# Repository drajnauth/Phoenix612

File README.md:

# Phoenix612
Phoenix612 Transceiver Board

This is the updated `Dueling 612 Tranceiver`.  It contains the KiCad schematic and pcb files as well as other design artifacts.

The project has been renamed to `Phoenix612`

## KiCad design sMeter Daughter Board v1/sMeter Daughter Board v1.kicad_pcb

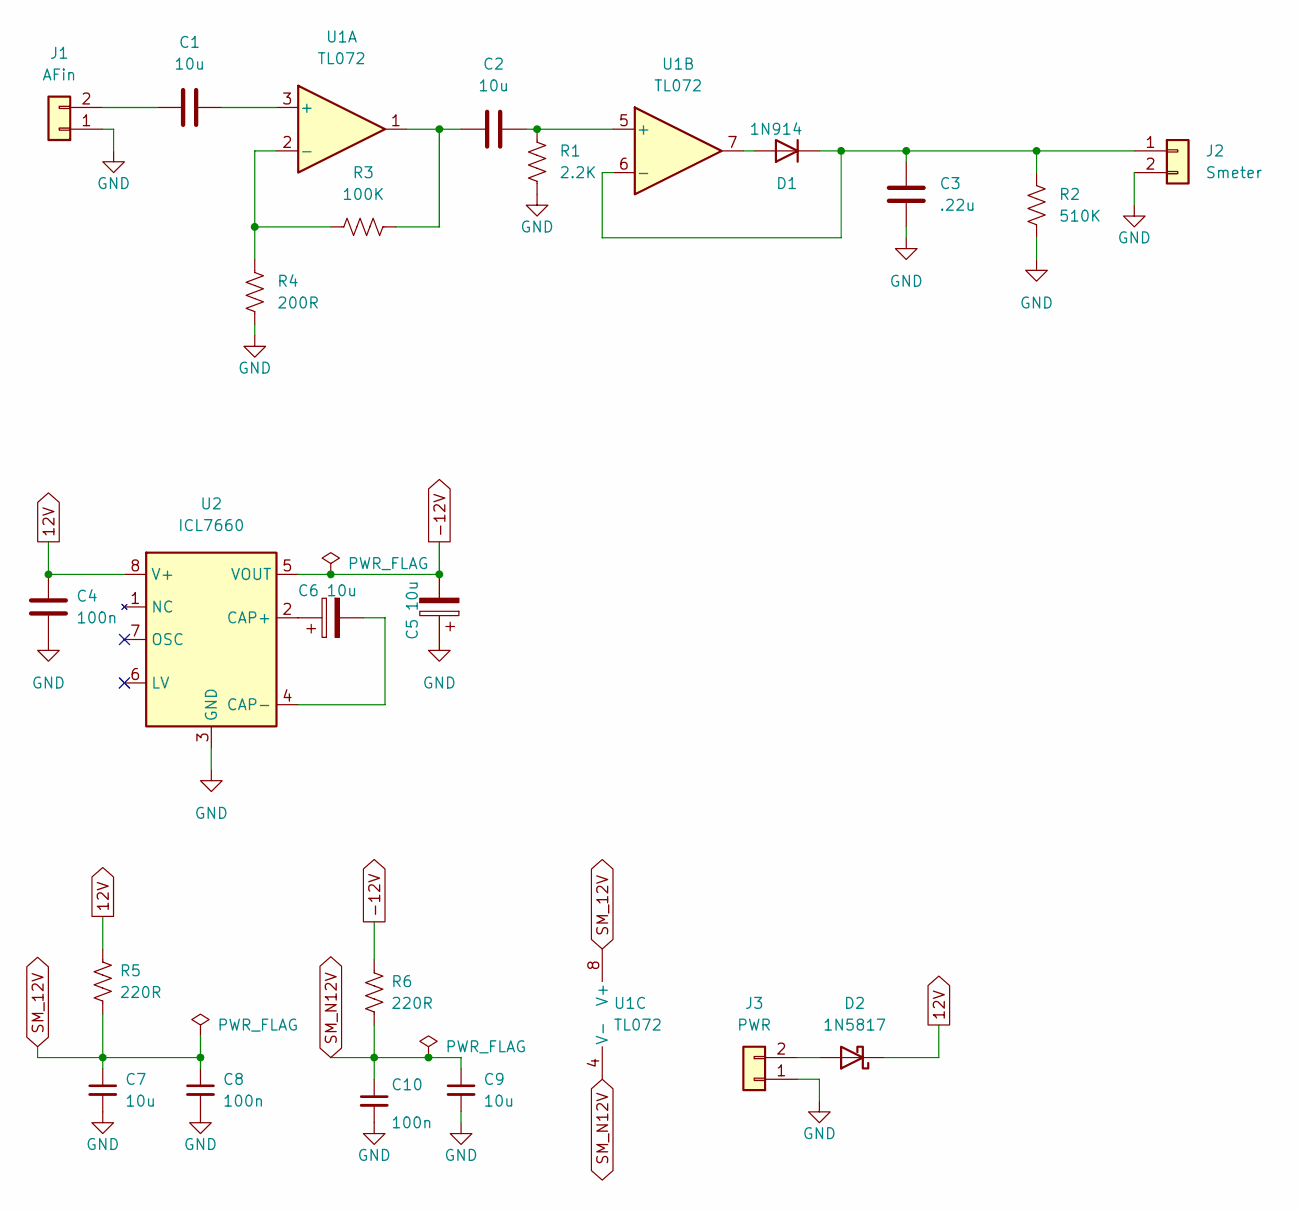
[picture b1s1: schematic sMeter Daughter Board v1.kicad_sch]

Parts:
C1, C2, C7, C9: 10u; C_1206_3216Metric
C3: .22u; C_1206_3216Metric
C4, C8, C10: 100n; C_1206_3216Metric
C5, C6: 10u; CP_Radial_D8.0mm_P2.50mm
D1: 1N914; D_DO-35_SOD27_P7.62mm_Horizontal
D2: 1N5817; D_DO-41_SOD81_P10.16mm_Horizontal
J1: AFin; PinHeader_1x02_P2.54mm_Vertical
J2: Smeter; PinHeader_1x02_P2.54mm_Vertical
J3: PWR; PinHeader_1x02_P2.54mm_Vertical
R1: 2.2K; R_1206_3216Metric
R2: 510K; R_1206_3216Metric
R3: 100K; R_1206_3216Metric
R4: 200R; R_1206_3216Metric
R5, R6: 220R; R_1206_3216Metric
U1: TL072; DIP-8_W7.62mm_Socket
U2: ICL7660; SOIC-8_3.9x4.9mm_P1.27mm

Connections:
12V: C4.2, D2.1 (K), R5.1, U2.8 (V+)
-12V: C5.2, R6.1, U2.5 (VOUT)
GND: C3.2, C4.1, C5.1, C7.2, C8.2, C9.2, C10.2, J1.1, J2.2, J3.1, R1.1, R2.1, R4.2, U2.3 (GND)
unnamed: C1.1, J1.2
unnamed: C1.2, U1.3 (+)
unnamed: C2.1, R3.2, U1.1
unnamed: C2.2, R1.2, U1.5 (+)
unnamed: C3.1, D1.1 (K), J2.1, R2.2, U1.6 (-)
unnamed: C6.1, U2.2 (CAP+)
unnamed: C6.2, U2.4 (CAP-)
unnamed: D1.2 (A), U1.7
unnamed: D2.2 (A), J3.2
unnamed: R3.1, R4.1, U1.2 (-)
SM_12V: C7.1, C8.1, R5.2, U1.8 (V+)
SM_N12V: C9.1, C10.1, R6.2, U1.4 (V-)

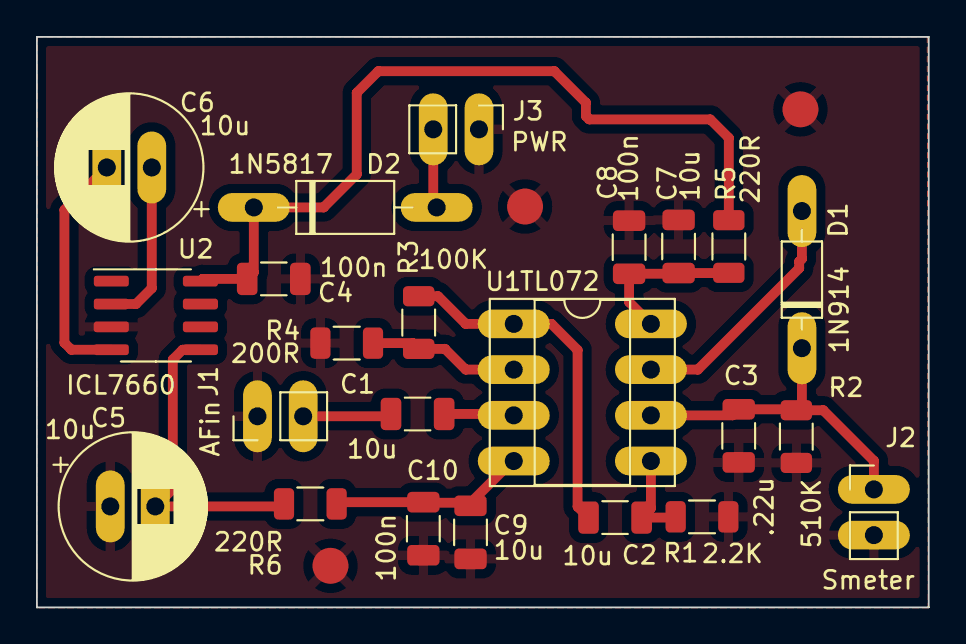
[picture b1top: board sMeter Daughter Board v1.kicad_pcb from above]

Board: 2 copper layers, 49.5 x 31.7 mm, 23 parts (0 on the bottom side), 15 nets.

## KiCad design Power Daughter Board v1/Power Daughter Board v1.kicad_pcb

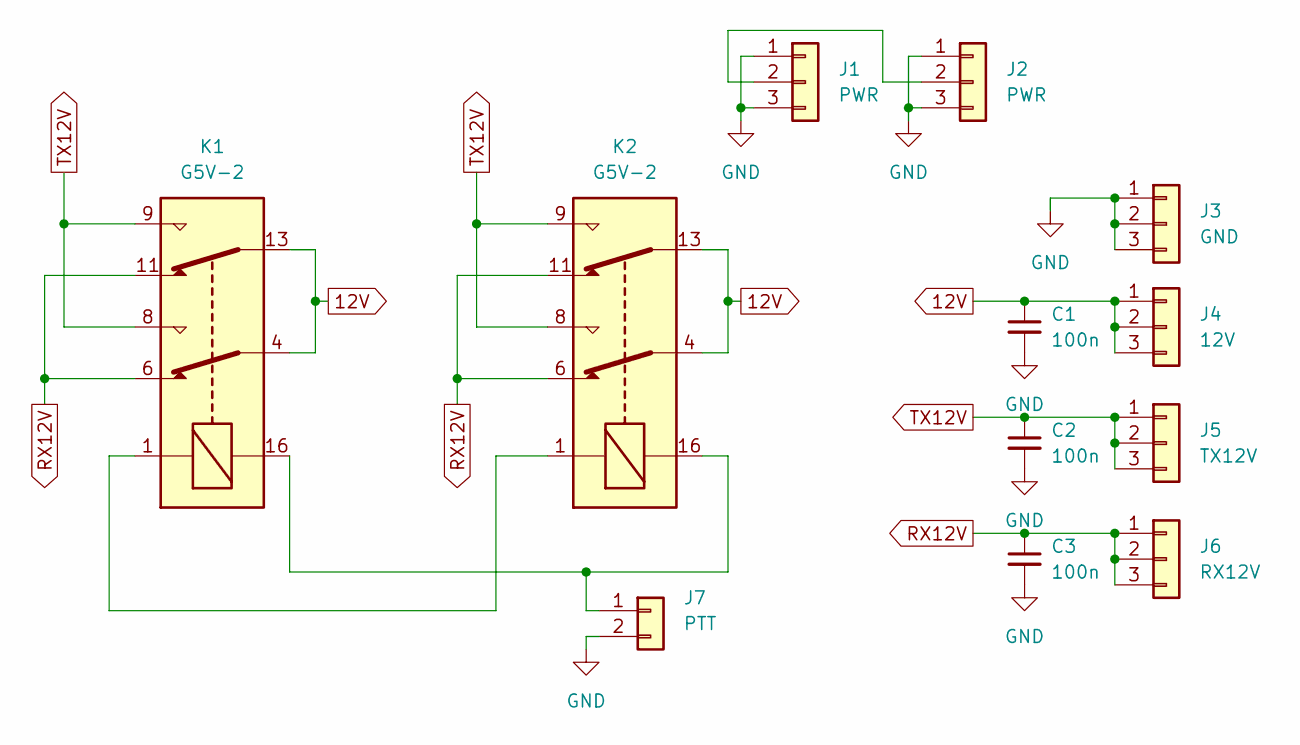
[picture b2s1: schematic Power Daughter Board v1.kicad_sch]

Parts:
C1, C2, C3: 100n; C_1206_3216Metric
J1, J2: PWR; PinHeader_1x03_P2.54mm_Vertical
J3: GND; PinHeader_1x03_P2.54mm_Vertical
J4: 12V; PinHeader_1x03_P2.54mm_Vertical
J5: TX12V; PinHeader_1x03_P2.54mm_Vertical
J6: RX12V; PinHeader_1x03_P2.54mm_Vertical
J7: PTT; PinHeader_1x02_P2.54mm_Vertical
K1, K2: G5V-2; Relay_DPDT_Omron_G5V-2

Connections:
12V: C1.1, J4.1, J4.2, J4.3, K1.4, K1.13, K2.4, K2.13
GND: C1.2, C2.2, C3.2, J1.1, J1.3, J2.1, J2.3, J3.1, J3.2, J3.3, J7.2
unnamed: J1.2, J2.2
unnamed: J7.1, K1.16, K2.16
unnamed: K1.1, K2.1
RX12V: C3.1, J6.1, J6.2, J6.3, K1.6, K1.11, K2.6, K2.11
TX12V: C2.1, J5.1, J5.2, J5.3, K1.8, K1.9, K2.8, K2.9

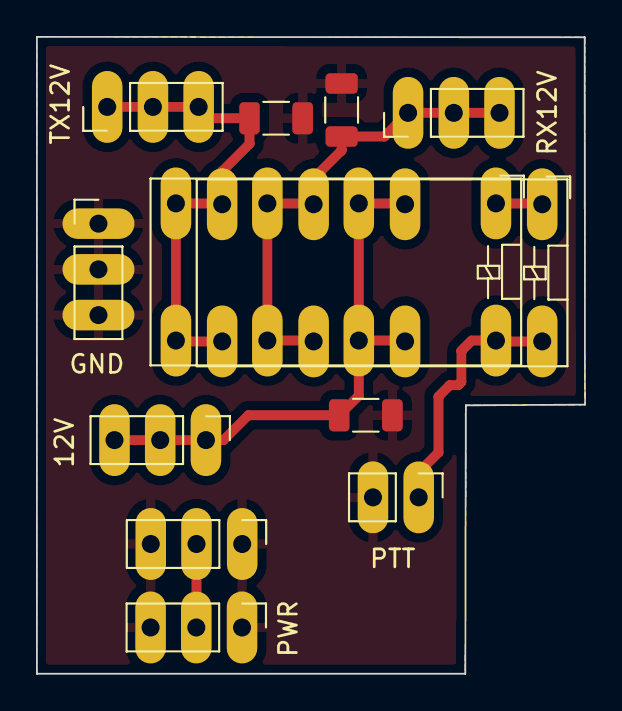
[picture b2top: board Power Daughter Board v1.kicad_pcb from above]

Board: 2 copper layers, 30.5 x 35.4 mm, 12 parts (0 on the bottom side), 7 nets.

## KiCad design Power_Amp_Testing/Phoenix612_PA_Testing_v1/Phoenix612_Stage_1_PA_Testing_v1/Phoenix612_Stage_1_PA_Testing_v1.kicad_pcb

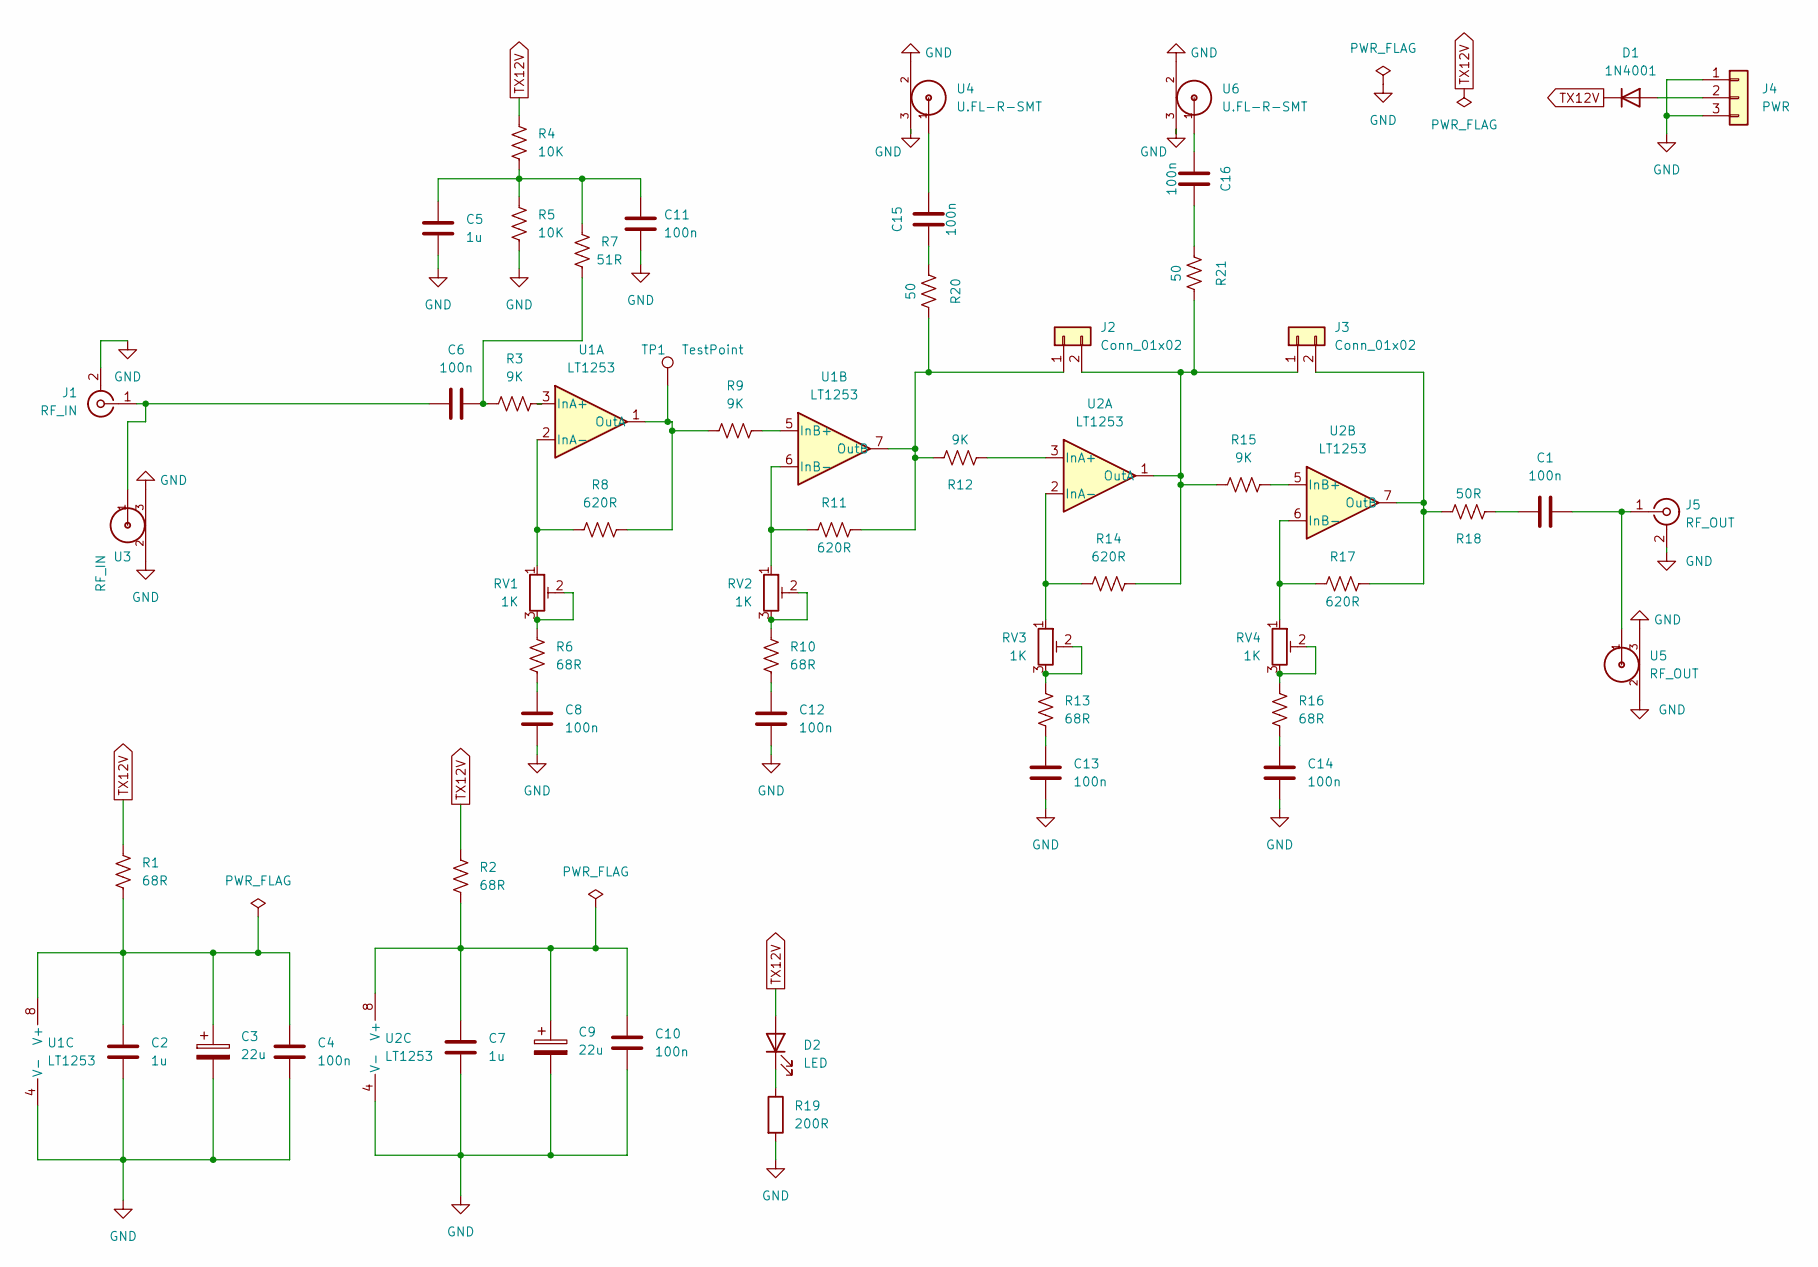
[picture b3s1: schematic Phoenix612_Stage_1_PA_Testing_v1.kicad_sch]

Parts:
C1, C4, C6, C8, C10, C11, C12, C13, C14, C15, C16: 100n; C_1206_3216Metric
C2, C5, C7: 1u; C_1206_3216Metric
C3, C9: 22u; CP_Radial_D8.0mm_P2.50mm
D1: 1N4001; D_DO-41_SOD81_P10.16mm_Horizontal
D2: LED; LED_D3.0mm
J1: RF_IN; SMA_Amphenol_901-144_Vertical
J2, J3: Conn_01x02; PinHeader_1x02_P2.54mm_Vertical
J4: PWR; PinHeader_1x03_P2.54mm_Vertical
J5: RF_OUT; SMA_Amphenol_901-144_Vertical
R1, R2, R6, R10, R13, R16: 68R; R_1206_3216Metric
R3, R9, R12, R15: 9K; R_1206_3216Metric
R4, R5: 10K; R_1206_3216Metric
R7: 51R; R_1206_3216Metric
R8, R11, R14, R17: 620R; R_1206_3216Metric
R18: 50R; R_1206_3216Metric
R19: 200R; R_1206_3216Metric
R20, R21: 50; R_1206_3216Metric
RV1, RV2, RV3, RV4: 1K; Potentiometer_Bourns_3296W_Vertical
TP1: TestPoint; Pin_D0.7mm_L6.5mm_W1.8mm_FlatFork
U1, U2: LT1253; DIP-8_W7.62mm
U3: RF_IN; U.FL-R-SMT
U4, U6: U.FL-R-SMT
U5: RF_OUT; U.FL-R-SMT

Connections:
GND: C2.2, C3.2, C4.2, C5.2, C7.2, C8.2, C9.2, C10.2, C11.2, C12.2, C13.2, C14.2, J1.2 (Ext), J4.1, J4.3, J5.2 (Ext), R5.2, R19.2, U1.4 (V-), U2.4 (V-), U3.2, U3.3, U4.2, U4.3, U5.2, U5.3, U6.2, U6.3
unnamed: C2.1, C3.1, C4.1, R1.2, U1.8 (V+)
unnamed: C6.1, J1.1 (In), U3.1
unnamed: C6.2, R3.1, R7.1
unnamed: C8.1, R6.2
unnamed: C7.1, C9.1, C10.1, R2.2, U2.8 (V+)
unnamed: C5.1, C11.1, R4.2, R5.1, R7.2
unnamed: C12.1, R10.2
unnamed: C13.1, R13.2
unnamed: C14.1, R16.2
unnamed: C15.1, R20.2
unnamed: C15.2, U4.1
unnamed: C16.2, R21.2
unnamed: D1.2 (A), J4.2
unnamed: D2.1 (K), R19.1
unnamed: C1.2, J5.1 (In), U5.1
unnamed: R3.2, U1.3 (InA+)
unnamed: R6.1, RV1.2, RV1.3
unnamed: R8.1, RV1.1, U1.2 (InA-)
unnamed: R8.2, R9.1, TP1.1, U1.1 (OutA)
unnamed: R9.2, U1.5 (InB+)
unnamed: R10.1, RV2.2, RV2.3
unnamed: J2.1, R11.1, R12.1, R20.1, U1.7 (OutB)
unnamed: R11.2, RV2.1, U1.6 (InB-)
unnamed: R13.1, RV3.2, RV3.3
unnamed: R14.1, RV3.1, U2.2 (InA-)
unnamed: J2.2, J3.1, R14.2, R15.1, R21.1, U2.1 (OutA)
unnamed: R15.2, U2.5 (InB+)
unnamed: R16.1, RV4.2, RV4.3
unnamed: J3.2, R17.1, R18.1, U2.7 (OutB)
unnamed: R17.2, RV4.1, U2.6 (InB-)
unnamed: C1.1, R18.2
unnamed: R12.2, U2.3 (InA+)
unnamed: C16.1, U6.1
TX12V: D1.1 (K), D2.2 (A), R1.1, R2.1, R4.1

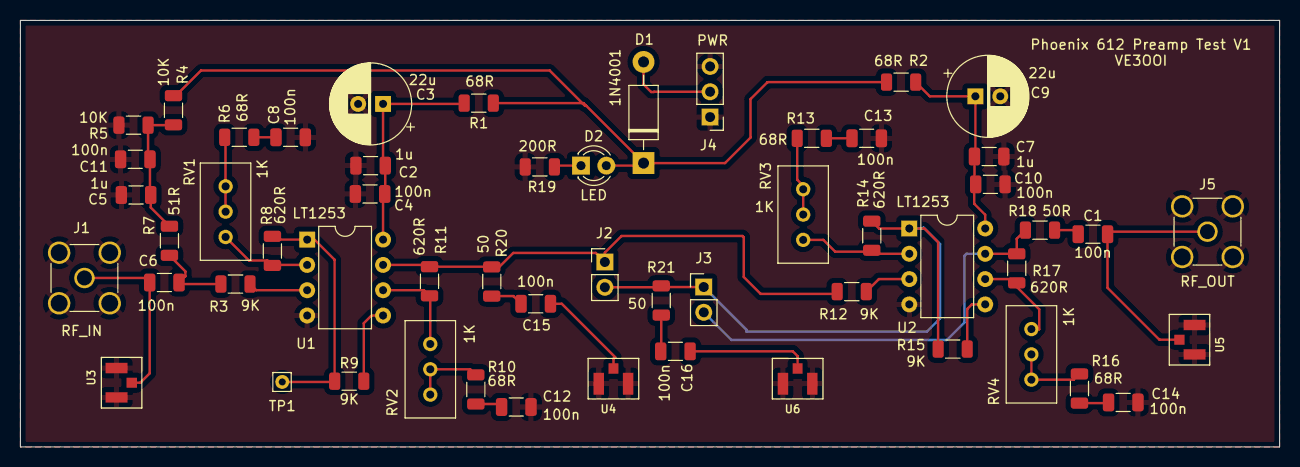
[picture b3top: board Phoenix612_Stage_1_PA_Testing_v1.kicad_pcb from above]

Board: 2 copper layers, 126.4 x 42.8 mm, 55 parts (0 on the bottom side), 35 nets.

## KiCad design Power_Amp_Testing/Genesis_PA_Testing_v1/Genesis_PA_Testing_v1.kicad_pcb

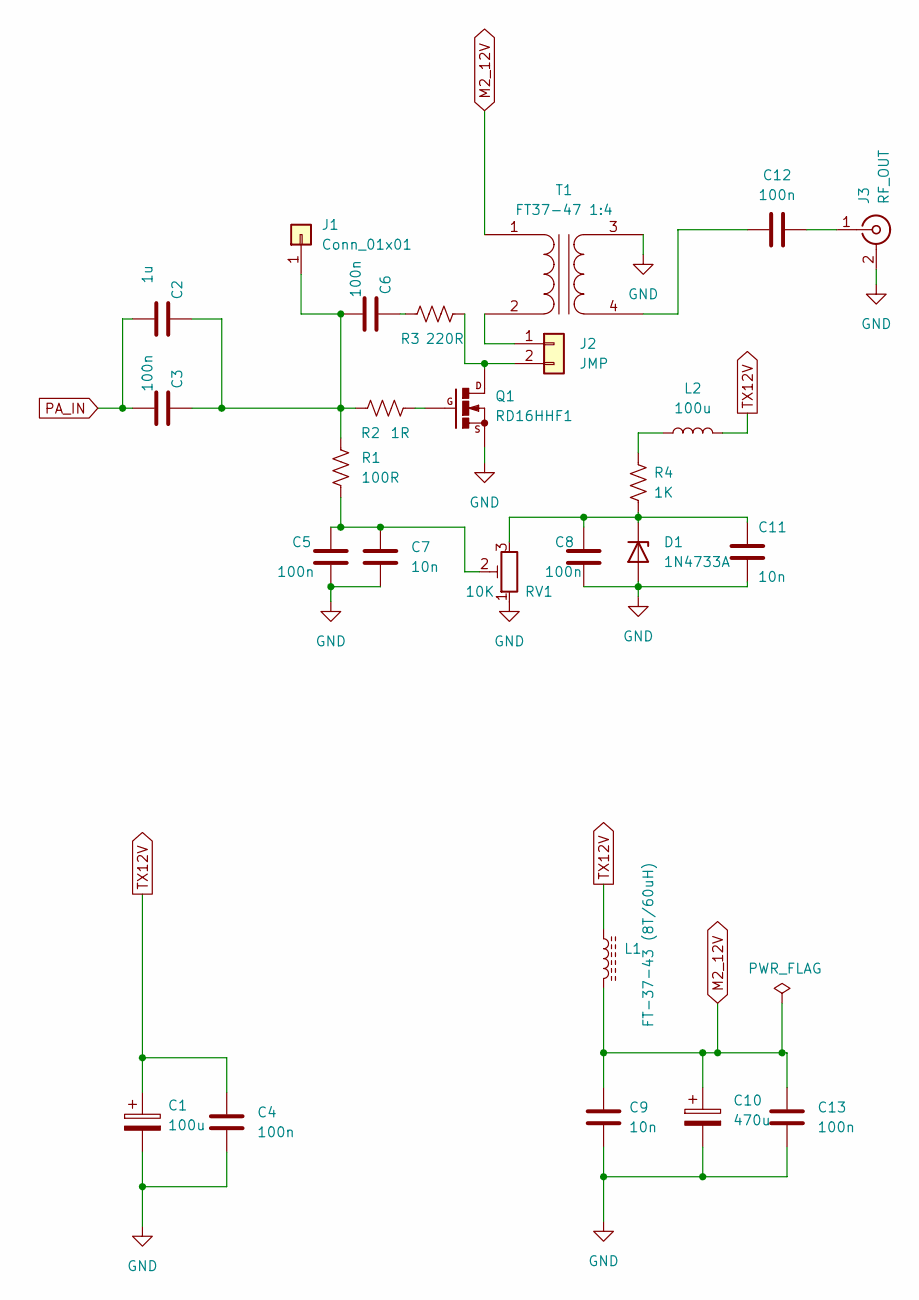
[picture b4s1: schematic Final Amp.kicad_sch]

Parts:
C1: 100u; CP_Radial_D8.0mm_P2.50mm
C2: 1u; C_1206_3216Metric
C3, C4, C5, C6, C8, C12, C13: 100n; C_1206_3216Metric
C7, C9, C11: 10n; C_1206_3216Metric
C10: 470u; CP_Radial_D8.0mm_P2.50mm
D1: 1N4733A; D_DO-41_SOD81_P10.16mm_Horizontal
J1: Conn_01x01; PinHeader_1x01_P1.00mm_Vertical
J2: JMP; PinHeader_1x02_P2.54mm_Vertical
J3: RF_OUT; SMA_Amphenol_901-144_Vertical
L1: FT-37-43 (8T/60uH); L_Toroid_Horizontal_D9.5mm_P15.00mm_Diameter10-5mm_Amidon-T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
L2: 100u; L_1206_3216Metric_Pad1.42x1.75mm_HandSolder
Q1: RD16HHF1; TO-220-3
R1: 100R; R_1206_3216Metric
R2: 1R; R_1206_3216Metric
R3: 220R; R_1206_3216Metric
R4: 1K; R_1206_3216Metric
RV1: 10K; Potentiometer_Bourns_3296W_Vertical
T1: FT37-47 1:4; Transformer_Toroid_Horizontal_D10.5mm_Amidon-T37

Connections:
GND: C1.2, C4.2, C5.2, C7.2, C8.2, C9.2, C10.2, C11.2, C13.2, D1.2 (A), J3.2 (Ext), Q1.2, RV1.1, T1.3 (SB); also elsewhere on the board
M2_12V: C9.1, C10.1, C13.1, L1.2, T1.1 (AA)
unnamed: C2.1, C3.1, C6.2, J1.1, R1.2, R2.2
unnamed: C5.1, C7.1, R1.1, RV1.2
unnamed: C6.1, R3.2
unnamed: C8.1, C11.1, D1.1 (K), R4.2, RV1.3
unnamed: C12.1, T1.4 (SA)
unnamed: C12.2, J3.1 (In)
unnamed: J2.1, T1.2 (AB)
unnamed: J2.2, Q1.3, R3.1
unnamed: L2.1, R4.1
unnamed: Q1.1, R2.1
PA_IN: C2.2, C3.2; also elsewhere on the board
TX12V: C1.1, C4.1, L1.1, L2.2; also elsewhere on the board

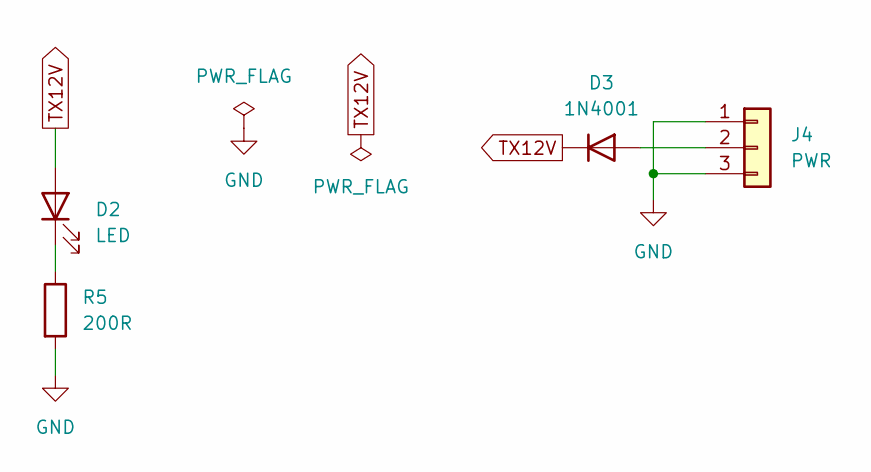
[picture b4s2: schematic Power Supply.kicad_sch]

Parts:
D2: LED; LED_D3.0mm
D3: 1N4001; D_DO-41_SOD81_P10.16mm_Horizontal
J4: PWR; PinHeader_1x03_P2.54mm_Vertical
R5: 200R; R_1206_3216Metric

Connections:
GND: J4.1, J4.3, R5.2; also elsewhere on the board
unnamed: D2.1 (K), R5.1
unnamed: D3.2 (A), J4.2
TX12V: D2.2 (A), D3.1 (K); also elsewhere on the board

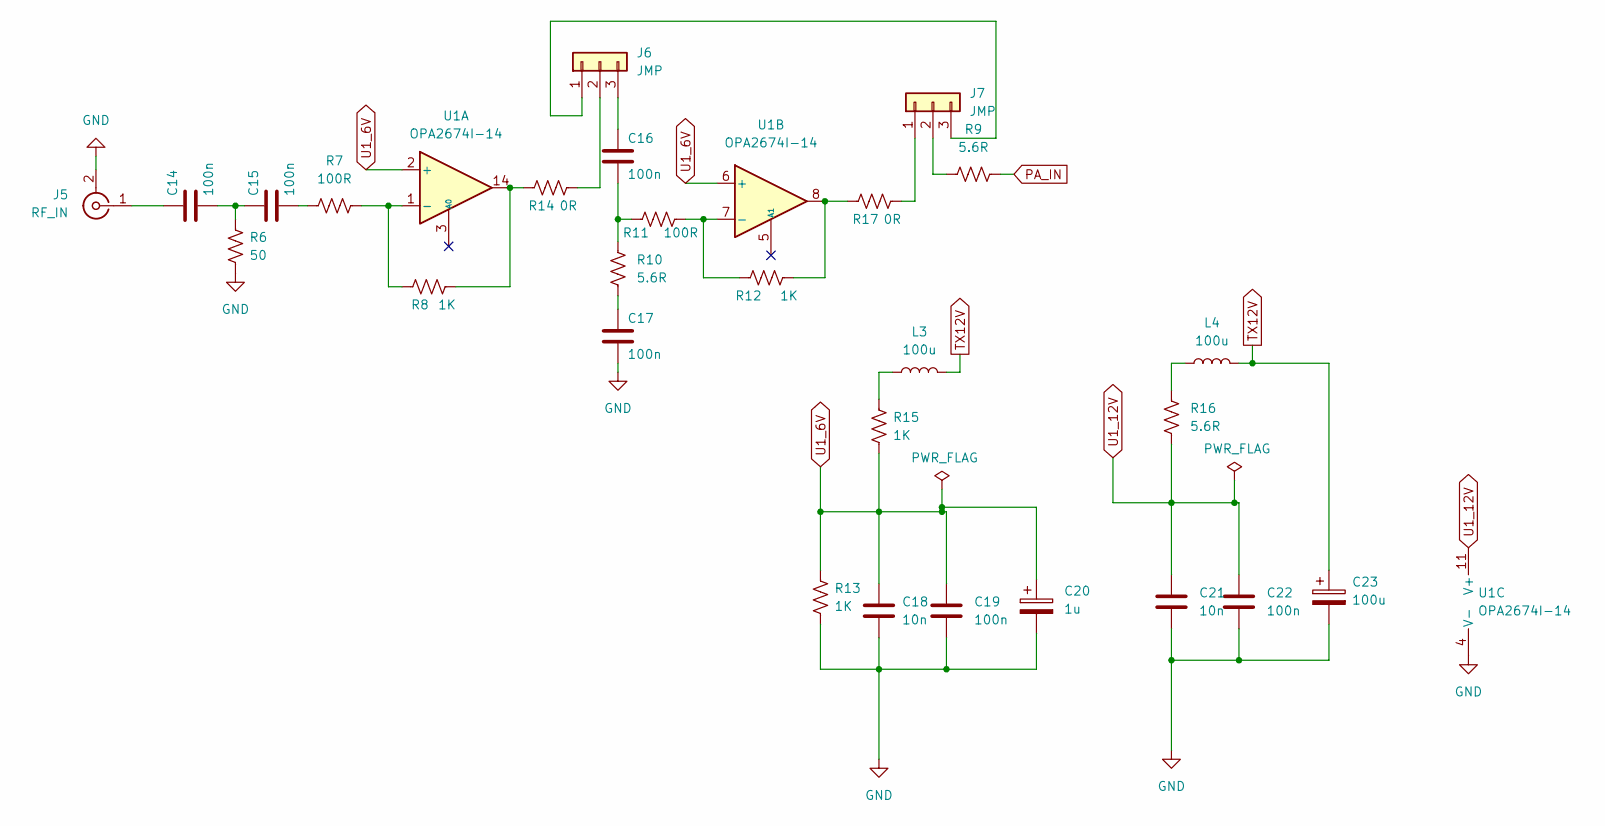
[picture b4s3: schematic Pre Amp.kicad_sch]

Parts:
C14, C15, C16, C17, C19, C22: 100n; C_1206_3216Metric
C18, C21: 10n; C_1206_3216Metric
C20: 1u; CP_Radial_D5.0mm_P2.50mm
C23: 100u; CP_Radial_D5.0mm_P2.50mm
J5: RF_IN; SMA_Amphenol_901-144_Vertical
J6, J7: JMP; PinHeader_1x03_P2.54mm_Vertical
L3, L4: 100u; L_1206_3216Metric_Pad1.42x1.75mm_HandSolder
R6: 50; R_1206_3216Metric
R7: 100R; R_1206_3216Metric
R8, R12: 1K; R_Axial_DIN0207_L6.3mm_D2.5mm_P7.62mm_Horizontal
R9: 5.6R; R_1206_3216Metric_Pad1.30x1.75mm_HandSolder
R10, R16: 5.6R; R_1206_3216Metric
R11: 100R; R_Axial_DIN0207_L6.3mm_D2.5mm_P7.62mm_Horizontal
R13, R15: 1K; R_1206_3216Metric
R14, R17: 0R; R_Axial_DIN0207_L6.3mm_D2.5mm_P7.62mm_Horizontal
U1: OPA2674I-14; SOIC-14_3.9x8.7mm_P1.27mm

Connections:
GND: C17.2, C18.2, C19.2, C20.2, C21.2, C22.2, C23.2, J5.2 (Ext), R6.1, R13.2, U1.4 (V-); also elsewhere on the board
unnamed: C14.1, J5.1 (In)
unnamed: C14.2, C15.1, R6.2
unnamed: C15.2, R7.1
unnamed: C16.1, J6.3
unnamed: C16.2, R10.2, R11.1
unnamed: C17.1, R10.1
unnamed: J6.1, J7.3
unnamed: J6.2, R14.2
unnamed: J7.1, R17.2
unnamed: J7.2, R9.1
unnamed: L3.1, R15.1
unnamed: L4.1, R16.1
unnamed: R7.2, R8.1, U1.1 (-)
unnamed: R8.2, R14.1, U1.14
unnamed: R11.2, R12.1, U1.7 (-)
unnamed: R12.2, R17.1, U1.8
PA_IN: R9.2; also elsewhere on the board
TX12V: C23.1, L3.2, L4.2; also elsewhere on the board
U1_6V: C18.1, C19.1, C20.1, R13.1, R15.2, U1.2 (+), U1.6 (+)
U1_12V: C21.1, C22.1, R16.2, U1.11 (V+)

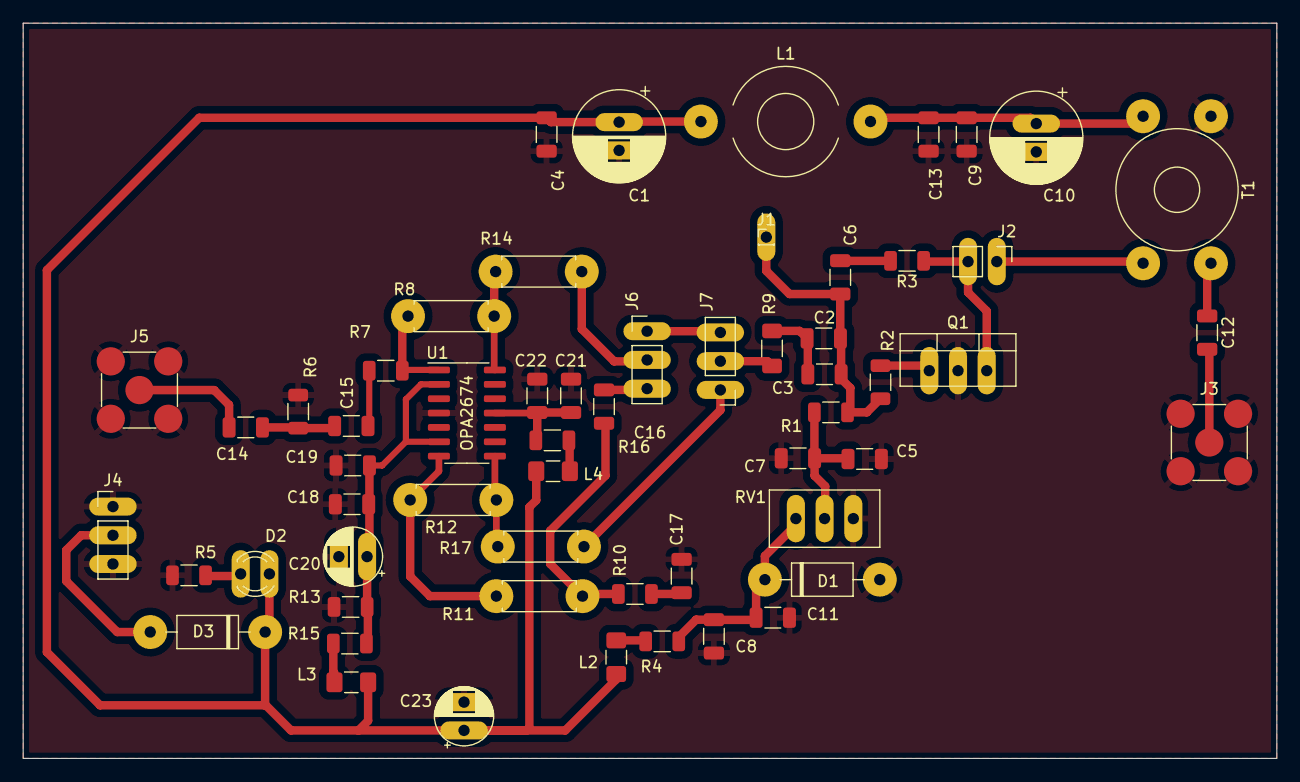
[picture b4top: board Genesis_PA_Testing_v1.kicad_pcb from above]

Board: 2 copper layers, 110.9 x 65.0 mm, 58 parts (0 on the bottom side), 34 nets.

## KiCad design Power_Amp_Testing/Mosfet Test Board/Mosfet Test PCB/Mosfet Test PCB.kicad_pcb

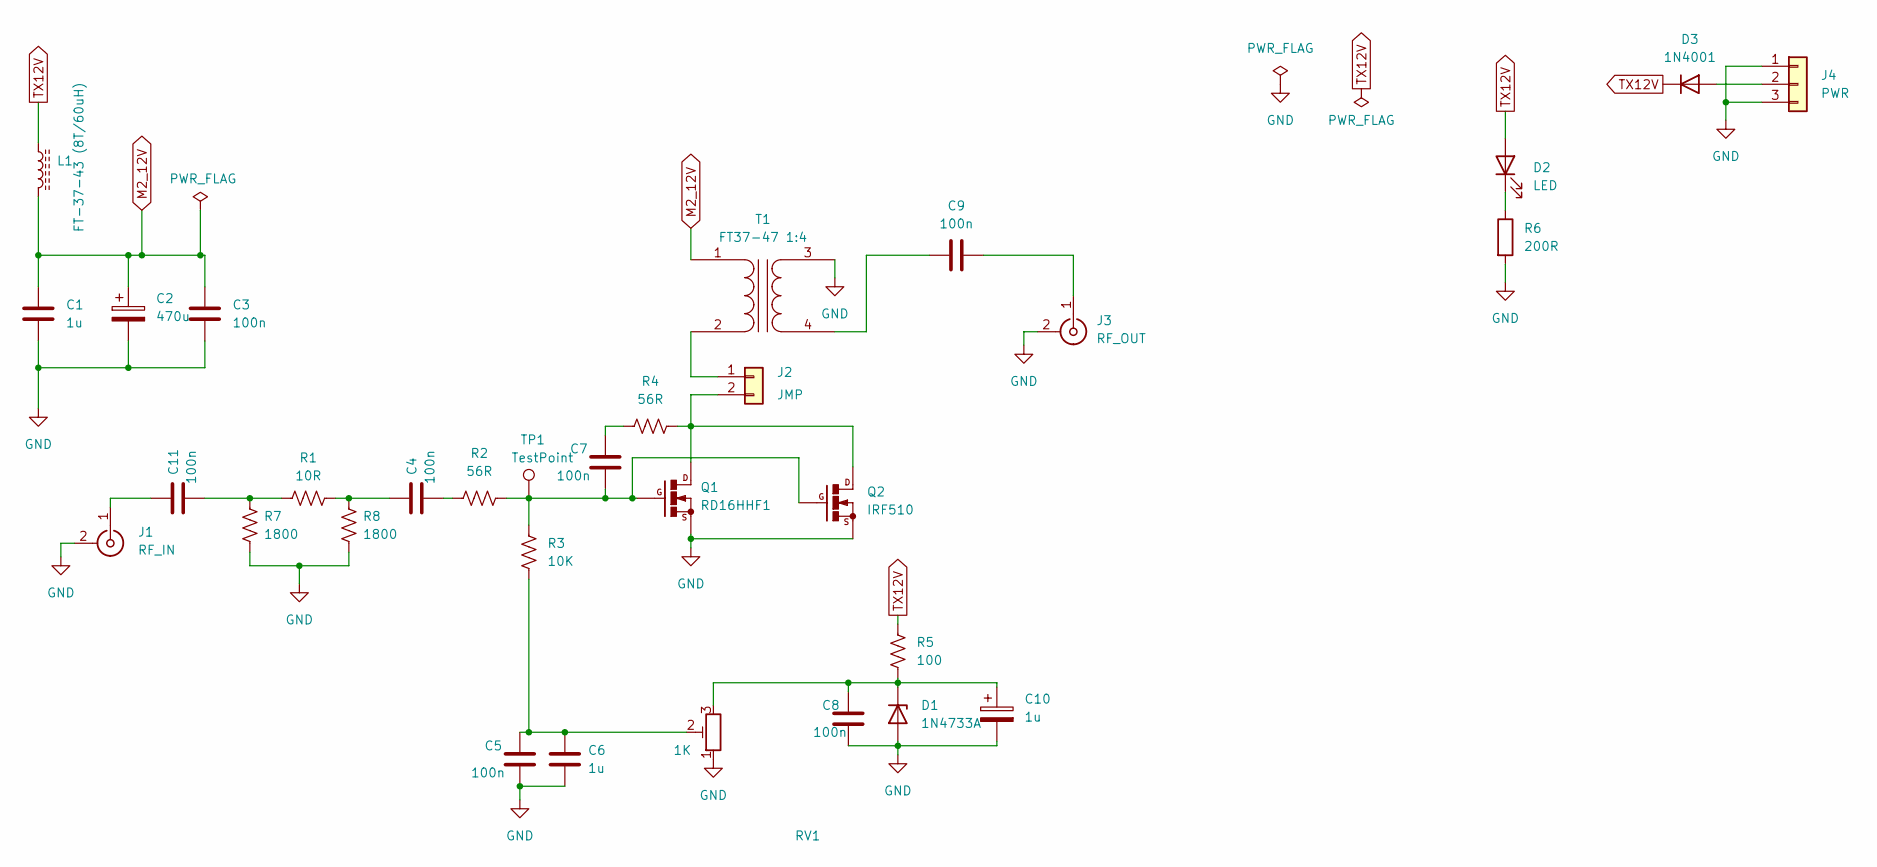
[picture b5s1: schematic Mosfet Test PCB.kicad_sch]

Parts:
C1, C6: 1u; C_1206_3216Metric
C2: 470u; CP_Radial_D8.0mm_P2.50mm
C3, C4, C5, C7, C8, C9, C11: 100n; C_1206_3216Metric
C10: 1u; CP_Radial_D8.0mm_P2.50mm
D1: 1N4733A; D_DO-41_SOD81_P10.16mm_Horizontal
D2: LED; LED_D3.0mm
D3: 1N4001; D_DO-41_SOD81_P10.16mm_Horizontal
J1: RF_IN; SMA_Amphenol_901-144_Vertical
J2: JMP; PinHeader_1x02_P2.54mm_Vertical
J3: RF_OUT; SMA_Amphenol_901-144_Vertical
J4: PWR; PinHeader_1x03_P2.54mm_Vertical
L1: FT-37-43 (8T/60uH); L_Toroid_Horizontal_D9.5mm_P15.00mm_Diameter10-5mm_Amidon-T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
Q1: RD16HHF1; TO-220-3
Q2: IRF510; TO220
R1: 10R; R_1206_3216Metric
R2, R4: 56R; R_1206_3216Metric
R3: 10K; R_1206_3216Metric
R5: 100; R_1206_3216Metric
R6: 200R; R_1206_3216Metric
R7, R8: 1800; R_1206_3216Metric
RV1: 1K; Potentiometer_Bourns_3296W_Vertical
T1: FT37-47 1:4; Transformer_Toroid_Horizontal_D10.5mm_Amidon-T37
TP1: TestPoint; Pin_D0.7mm_L6.5mm_W1.8mm_FlatFork

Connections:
GND: C1.2, C2.2, C3.2, C5.2, C6.2, C8.2, C10.2, D1.2 (A), J1.2 (Ext), J3.2 (Ext), J4.1, J4.3, Q1.2, Q2.1, R6.2, R7.2, R8.2, RV1.1, T1.3 (SB)
M2_12V: C1.1, C2.1, C3.1, L1.2, T1.1 (AA)
unnamed: C4.1, R1.1, R8.1
unnamed: C4.2, R2.2
unnamed: C5.1, C6.1, R3.1, RV1.2
unnamed: C7.1, R4.2
unnamed: C7.2, Q1.1, Q2.3, R2.1, R3.2, TP1.1
unnamed: C9.1, T1.4 (SA)
unnamed: C9.2, J3.1 (In)
unnamed: C8.1, C10.1, D1.1 (K), R5.2, RV1.3
unnamed: D2.1 (K), R6.1
unnamed: D3.2 (A), J4.2
unnamed: C11.1, J1.1 (In)
unnamed: J2.1, T1.2 (AB)
unnamed: J2.2, Q1.3, Q2.2, R4.1
unnamed: C11.2, R1.2, R7.1
TX12V: D2.2 (A), D3.1 (K), L1.1, R5.1

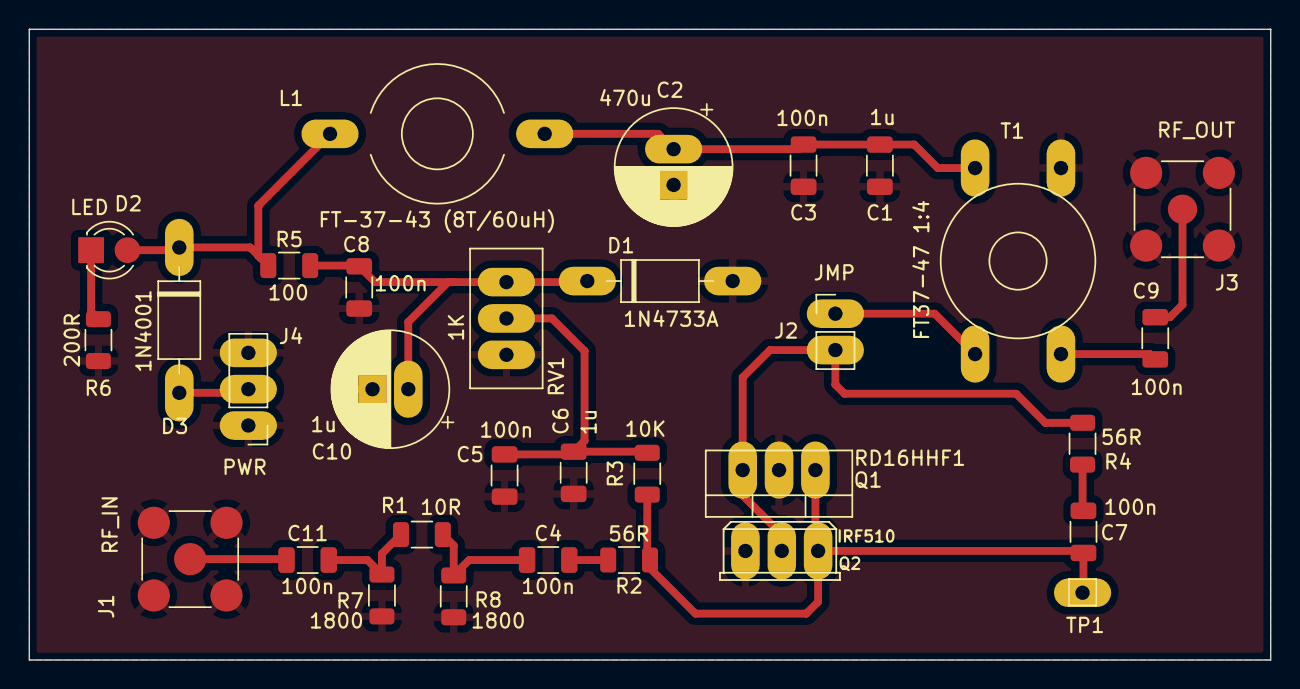
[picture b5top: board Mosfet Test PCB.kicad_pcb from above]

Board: 2 copper layers, 86.7 x 44.1 mm, 32 parts (0 on the bottom side), 17 nets.

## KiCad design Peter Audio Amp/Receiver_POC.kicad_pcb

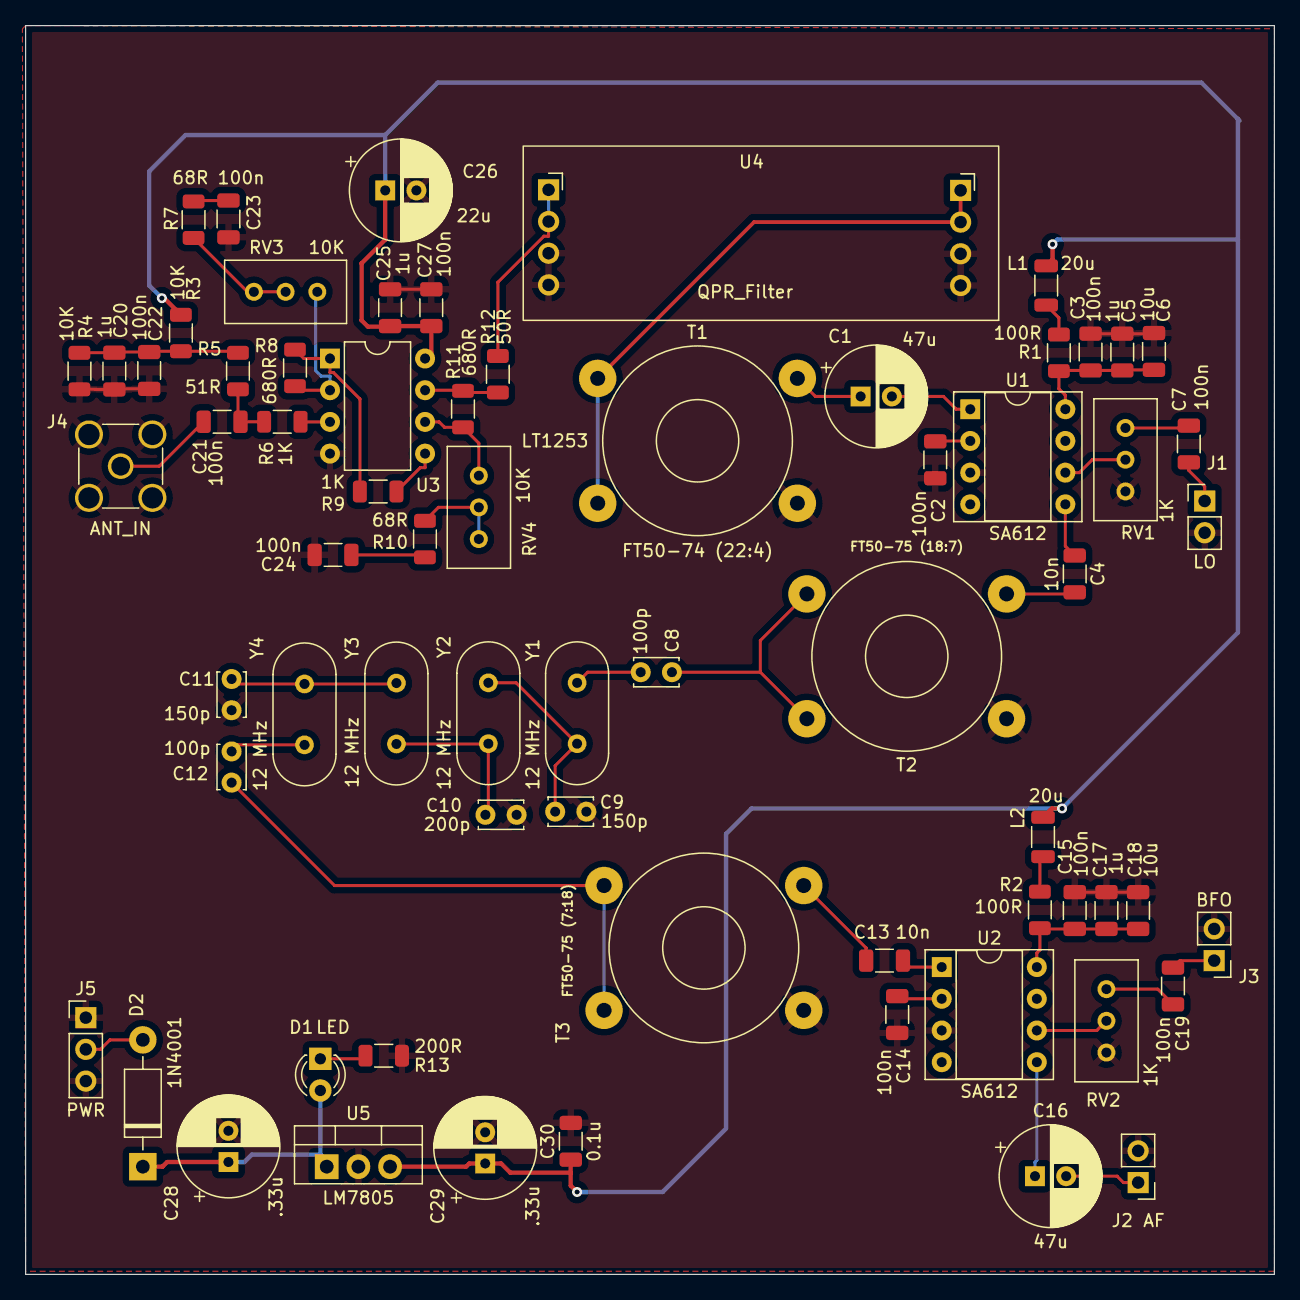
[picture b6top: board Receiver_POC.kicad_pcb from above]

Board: 2 copper layers, 100.1 x 100.1 mm, 68 parts (0 on the bottom side), 47 nets.

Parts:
C1, C16: 47u; CP_Radial_D8.0mm_P2.50mm
C2, C3, C7, C14, C15, C19, C21, C22, C23, C24, C27: 100n; C_1206_3216Metric
C4, C13: 10n; C_1206_3216Metric
C5, C17, C20, C25: 1u; C_1206_3216Metric
C6, C18: 10u; C_1206_3216Metric
C8, C12: 100p; C_Disc_D3.4mm_W2.1mm_P2.50mm
C9, C11: 150p; C_Disc_D3.4mm_W2.1mm_P2.50mm
C10: 200p; C_Disc_D3.4mm_W2.1mm_P2.50mm
C26: 22u; CP_Radial_D8.0mm_P2.50mm
C28, C29: .33u; CP_Radial_D8.0mm_P2.50mm
C30: 0.1u; C_1206_3216Metric
D1: LED; LED_D3.0mm
D2: 1N4001; D_DO-41_SOD81_P10.16mm_Horizontal
J1: LO; PinHeader_1x02_P2.54mm_Vertical
J2: AF; PinHeader_1x02_P2.54mm_Vertical
J3: BFO; PinHeader_1x02_P2.54mm_Vertical
J4: ANT_IN; SMA_Amphenol_901-144_Vertical
J5: PWR; PinHeader_1x03_P2.54mm_Vertical
L1, L2: 20u; L_1206_3216Metric
R1, R2: 100R; R_1206_3216Metric
R3, R4: 10K; R_1206_3216Metric
R5: 51R; R_1206_3216Metric
R6, R9: 1K; R_1206_3216Metric
R7, R10: 68R; R_1206_3216Metric
R8, R11: 680R; R_1206_3216Metric
R12: 50R; R_1206_3216Metric
R13: 200R; R_1206_3216Metric
RV1, RV2: 1K; Potentiometer_Bourns_3296W_Vertical
RV3, RV4: 10K; Potentiometer_Bourns_3296W_Vertical
T1: FT50-74 (22:4); Transformer_Toroid_Horizontal_D14.0mm_Amidon-T50
T2: FT50-75 (18:7); Transformer_Toroid_Horizontal_D14.0mm_Amidon-T50
T3: FT50-75 (7:18); Transformer_Toroid_Horizontal_D14.0mm_Amidon-T50
U1, U2: SA612; DIP-8_W7.62mm_Socket
U3: LT1253; DIP-8_W7.62mm
U4: QPR_Filter; QRPLabs_Filter_TH
U5: LM7805; TO-220-3_Vertical
Y1, Y2, Y3, Y4: 12 MHz; Crystal_HC49-4H_Vertical

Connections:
12V: C28.1, D1.2 (A), D2.1 (K), U5.1 (VI)
GND: C2.2, C3.2, C5.2, C6.2, C9.2, C10.2, C11.2, C14.2, C15.2, C17.2, C18.2, C20.2, C22.2, C23.2, C24.2, C25.2, C26.2, C27.2, C28.2, C29.2, C30.2, J1.2, J2.2, J3.2, J4.2 (Ext), J5.1, J5.3, R4.2, R13.2, RV1.3, RV2.3, T1.2 (AB), T2.3 (SA), T3.2 (AB), U1.3 (GND), U2.3 (GND), U3.4 (V-), U4.3 (GND), U4.4 (GND), U4.5 (GND), U4.6 (GND), U5.2 (GND)
IFAFOUT: C16.2, J2.1
IFRFIN: T1.1 (AA), T1.3 (SA), U4.7 (OUT), U4.8 (OUT)
unnamed: C1.1, T1.4 (SB)
unnamed: C1.2, U1.1 (IN_A)
unnamed: C2.1, U1.2 (IN_B)
unnamed: C3.1, C5.1, C6.1, R1.2, U1.8 (Vcc)
unnamed: C4.1, U1.5 (OUT_B)
unnamed: C4.2, T2.1 (AA)
unnamed: C7.1, J1.1
unnamed: C7.2, RV1.1
unnamed: C8.1, T2.2 (AB), T2.4 (SB)
unnamed: C8.2, Y1.1
unnamed: C9.1, Y1.2, Y2.1
unnamed: C10.1, Y2.2, Y3.1
unnamed: C11.1, Y3.2, Y4.1
unnamed: C12.1, Y4.2
unnamed: C12.2, T3.1 (AA), T3.3 (SA)
unnamed: C13.1, T3.4 (SB)
unnamed: C13.2, U2.1 (IN_A)
unnamed: C14.1, U2.2 (IN_B)
unnamed: C15.1, C17.1, C18.1, R2.2, U2.8 (Vcc)
unnamed: C16.1, U2.5 (OUT_B)
unnamed: C19.1, J3.1
unnamed: C19.2, RV2.1
unnamed: C20.1, C22.1, R3.2, R4.1, R5.2
unnamed: C21.1, J4.1 (In)
unnamed: C21.2, R5.1, R6.1
unnamed: C23.1, R7.2
unnamed: C24.1, R10.2
unnamed: D1.1 (K), R13.1
unnamed: D2.2 (A), J5.2
unnamed: L1.2, R1.1
unnamed: L2.2, R2.1
unnamed: R6.2, U3.3 (InA+)
unnamed: R7.1, RV3.2, RV3.3
unnamed: R8.1, RV3.1, U3.2 (InA-)
unnamed: R8.2, R9.1, U3.1 (OutA)
unnamed: R9.2, U3.5 (InB+)
unnamed: R10.1, RV4.2, RV4.3
unnamed: R11.1, R12.1, U3.7 (OutB)
unnamed: R11.2, RV4.1, U3.6 (InB-)
unnamed: R12.2, U4.1 (IN), U4.2 (IN)
unnamed: RV1.2, U1.6 (OSC_B)
unnamed: RV2.2, U2.6 (OSC_B)
RX5V: C25.1, C26.1, C27.1, C29.1, C30.1, L1.1, L2.1, R3.1, U3.8 (V+), U5.3 (VO)
